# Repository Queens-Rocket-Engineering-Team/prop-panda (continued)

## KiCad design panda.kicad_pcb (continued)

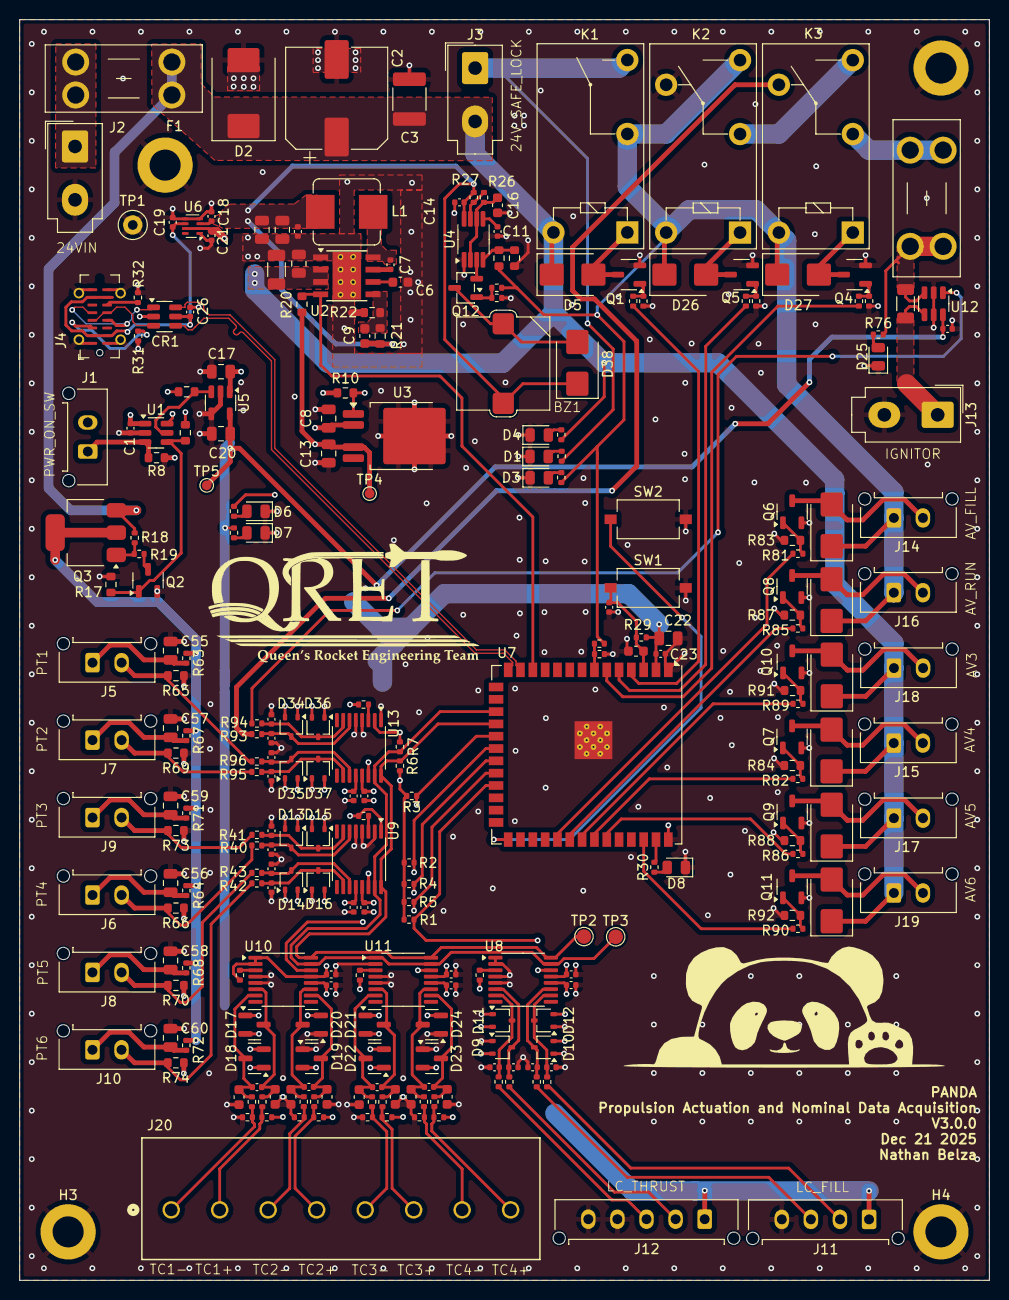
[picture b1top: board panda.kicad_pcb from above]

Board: 4 copper layers, 100.0 x 130.0 mm, 268 parts (0 on the bottom side), 135 nets.

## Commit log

2025-11-06 Update date
2025-11-07 minor fixed + lowered status leds to ~0.6mA, which should give ~50 mcd
2025-11-07 updated name on pcb
2025-11-09 revamped schematic to be more readable
2025-11-09 remove diode between 5V and 5V_USB due to oversight (ADS112C04 cannot have DVDD without AVDD)
2025-11-11 add power sequencing
    add usb VBUS ORing
2025-11-11 add thermocouple filtering, add 5th ADC
2025-11-11 grounded usb-c receptacle shield
2025-11-16 minor fixes
2025-11-17 add 2 stage lockout to ignitor, add ignitor resistance reading with adc current source
2025-11-17 fix ignitor resistance read circuit to use correct PGA reference
2025-11-17 add periodic buzzer alert to +24V_SAFE
2025-11-17 ground floating trace between ign relays when relays open
2025-11-21 add rc filters to pressure transducer power in to filter 500khz signal on 24v rail
2025-11-21 add some comments to clarify ign_resist_read circuitry and implementation
2025-11-22 change buck converter to hopefully remove some noise on 24v
2025-11-25 add capacitor and resistor footprints
2025-11-27 start pcb design
2025-12-01 change connectors and more progress on pcb
2025-12-06 change clamping resistors on tc adcs for lower leakage current
2025-12-21 Add identifying silkscreen text and icons
2025-12-21 Fix all silkscreen overlaps and violations
2025-12-21 Resolve DRC issues
2025-12-22 fix buzzer footprint to remove silkscreen pad overlap
2025-12-22 add silkscreen labels to connectors, remove pick Rb message (was already chosen)
2025-12-30 Update version number in KiCad files
2025-12-31 Update with new production files. Change CSA to INA187A2 (from A1 skew) for LCSC availability reasons.
2026-01-21 fix inverted usb lines
2026-01-21 fix usb data traces on pcb
2026-01-29 add nmos to buzzer to keep off when 24vSAFE off
2026-02-05 fix adc numbering
2026-02-07 fix usb traces to be 90 ohms impedance
2026-02-14 fix adc numbering on schematic
2026-02-15 add readme
2026-02-15 fix readme formatting
2026-02-15 fix drdy pin numbering
2026-02-17 update readme board picture
2026-02-20 Fix some wording in readme
2026-02-21 fix idac wording
2026-02-28 update board image again
